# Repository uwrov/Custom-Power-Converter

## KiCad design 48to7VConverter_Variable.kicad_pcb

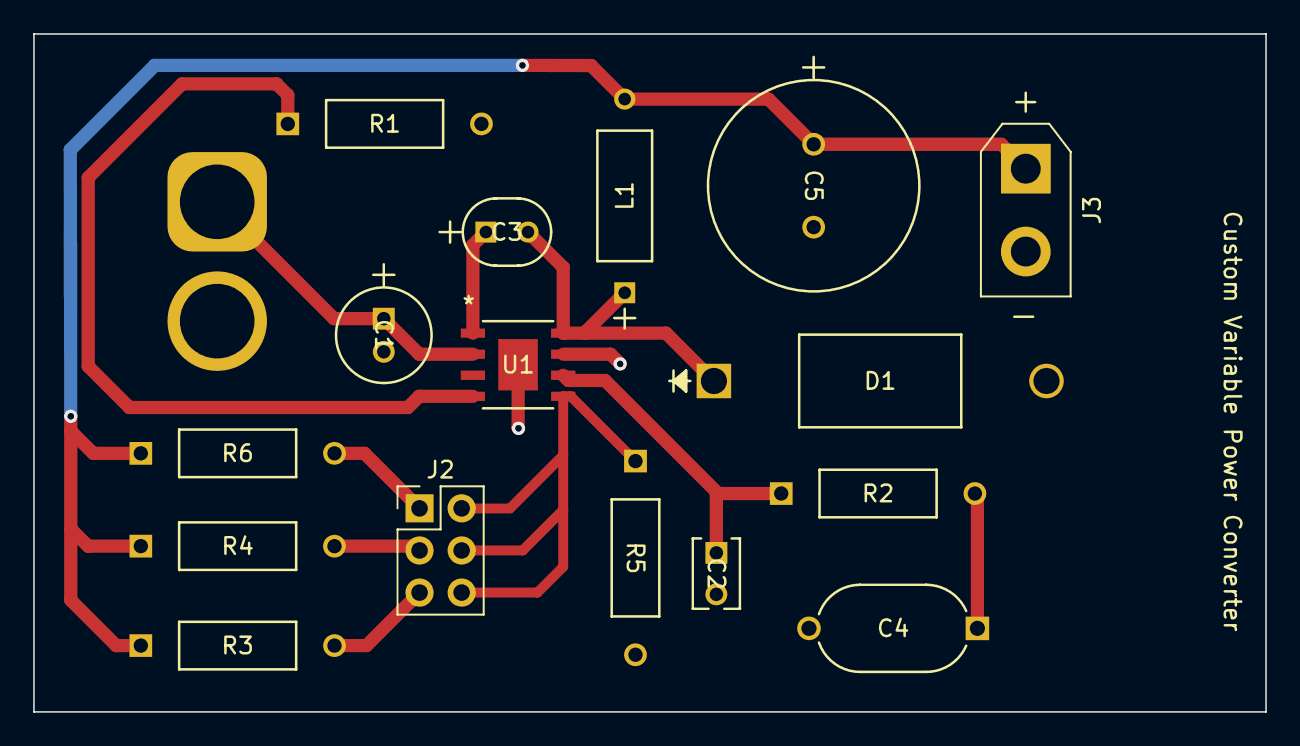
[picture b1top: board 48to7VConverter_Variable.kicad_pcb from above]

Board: 2 copper layers, 74.3 x 40.9 mm, 17 parts (1 on the bottom side), 12 nets.

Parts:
C1: 2.2uF; CAP_WCAP-ATG8_5x11_WRE
C2: 18pF; K180J15C0GF5TL2_VIS
C3: 100nF; CAP_C320_KEM
C4: 1nF; CAP_VY1_Y5U_9X5X13-10_VIS
C5: 47uF; CAP_UBX_12P5X20_NCH
D1: D_Schottky; DIODE_DO-201AD
J1: XT_60_In; AMASS_XT60-F_1x02_P7.20mm_Vertical
J2: Conn_02x03_Odd_Even; PinHeader_2x03_P2.54mm_Vertical
J3: XT_30_out; AMASS_XT30UPB-M_1x02_P5.0mm_Vertical
L1: 15uH; IND_BOURNS_8230
R1: 205k; YAG_MF25_YAG
R2: 28.7k; YAG_MF25_YAG
R3: 32k; YAG_MF25_YAG
R4: 53k; YAG_MF25_YAG
R5: 10k; YAG_MF25_YAG
R6: 80.6k; YAG_MF25_YAG
U1: TPS54360BDDAR; U_DDA_TEX

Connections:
/Feedback: J2.2, J2.4, J2.6, R5.1, U1.5 (FB)
/Vout: C5.1, J3.1, L1.2, R3.1, R4.1, R6.1
GND: C1.2, C2.2, C4.2, C5.2, D1.2 (A), J1.2, J3.2, R1.2, R5.2, U1.7 (GND), U1.EPAD
unnamed: C1.1, J1.1, U1.2 (VIN)
unnamed: C4.1, R2.2
unnamed: C3.2, D1.1 (K), L1.1, U1.8 (SW)
unnamed: J2.1, R6.2
unnamed: J2.3, R4.2
unnamed: J2.5, R3.2
unnamed: C3.1, U1.1 (BOOT)
unnamed: C2.1, R2.1, U1.6 (COMP)
unnamed: R1.1, U1.4 (RT/CLK)

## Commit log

2024-04-16 Add files via upload
    Schematic and PCB files
2024-04-16 Add files via upload
    Footprints used in the PCB
